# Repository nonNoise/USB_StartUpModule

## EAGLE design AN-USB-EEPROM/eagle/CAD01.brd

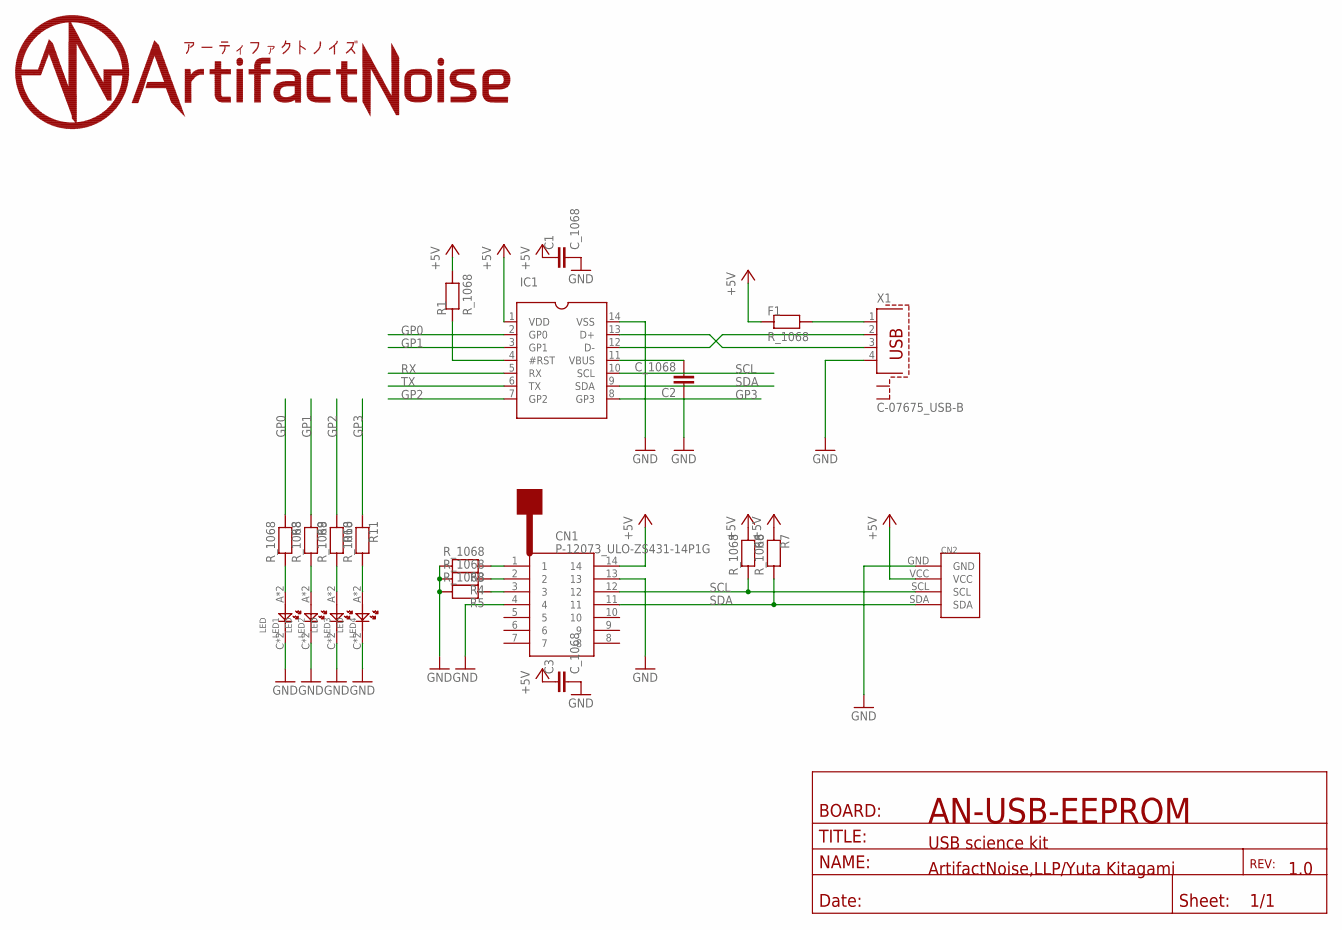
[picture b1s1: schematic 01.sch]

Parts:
C1, C2, C3: C_1068; C0603
CN1: P-12073_ULO-ZS431-14P1G; ULO-ZS431-14P1G
CN2: PIN4
F1: R_1068; R0603
IC1: _MCP2221A-I/PS; SOCKET-14
LED1, LED2, LED3, LED4: LED; CHIPLED_0805
R1, R3, R4, R5, R6, R7, R8, R9, R10, R11: R_1068; R0603
X1: C-07675_USB-B; PN61729-S

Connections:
+5V: C1.1, C1.D1 (1), C3.1, C3.D1 (1), CN1.14, CN2.VCC, F1.1, F1.D1 (1), IC1.1 (VDD), R1.2, R1.D2 (2), R6.1, R6.D1 (1), R7.1, R7.D1 (1)
GND: C1.2, C1.D2 (2), C2.1, C2.D1 (1), C3.2, C3.D2 (2), CN1.4, CN1.13, CN2.GND, IC1.14 (VSS), LED1.C, LED1.DC (C), LED2.C, LED2.DC (C), LED3.C, LED3.DC (C), LED4.C, LED4.DC (C), R3.2, R3.D2 (2), R4.2, R4.D2 (2), R5.2, R5.D2 (2), X1.4
GP0: IC1.2 (GP0), R8.1, R8.D1 (1)
GP1: IC1.3 (GP1), R9.1, R9.D1 (1)
GP2: IC1.7 (GP2), R10.1, R10.D1 (1)
GP3: IC1.8 (GP3), R11.1, R11.D1 (1)
unnamed: IC1.4 (#RST), R1.1, R1.D1 (1)
unnamed: IC1.13 (D+), X1.3
unnamed: IC1.12 (D-), X1.2
unnamed: C2.2, C2.D2 (2), IC1.11 (VBUS)
unnamed: F1.2, F1.D2 (2), X1.1
unnamed: CN1.1, R3.1, R3.D1 (1)
unnamed: CN1.2, R4.1, R4.D1 (1)
unnamed: CN1.3, R5.1, R5.D1 (1)
unnamed: LED1.A, LED1.DA (A), R8.2, R8.D2 (2)
unnamed: LED2.A, LED2.DA (A), R9.2, R9.D2 (2)
unnamed: LED3.A, LED3.DA (A), R10.2, R10.D2 (2)
unnamed: LED4.A, LED4.DA (A), R11.2, R11.D2 (2)
RX: IC1.5 (RX)
SCL: CN1.12, CN2.SCL, IC1.10 (SCL), R6.2, R6.D2 (2)
SDA: CN1.11, CN2.SDA, IC1.9 (SDA), R7.2, R7.D2 (2)
TX: IC1.6 (TX)

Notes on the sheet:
AN-USB-EEPROM
USB science kit
ArtifactNoise,LLP/Yuta Kitagami
1.0

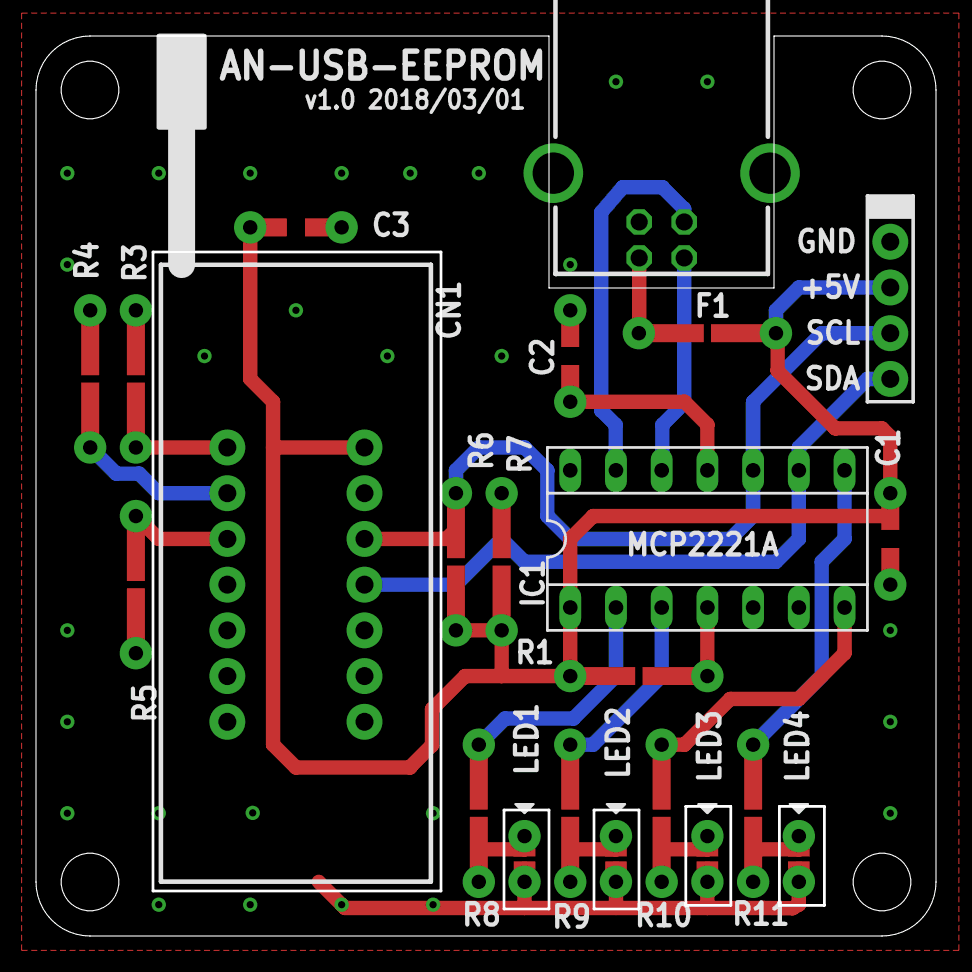
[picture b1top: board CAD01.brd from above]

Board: 2 copper layers, 50.0 x 50.0 mm, 23 parts (1 on the bottom side), 20 nets.

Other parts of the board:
U$1: AN-LOGO2
